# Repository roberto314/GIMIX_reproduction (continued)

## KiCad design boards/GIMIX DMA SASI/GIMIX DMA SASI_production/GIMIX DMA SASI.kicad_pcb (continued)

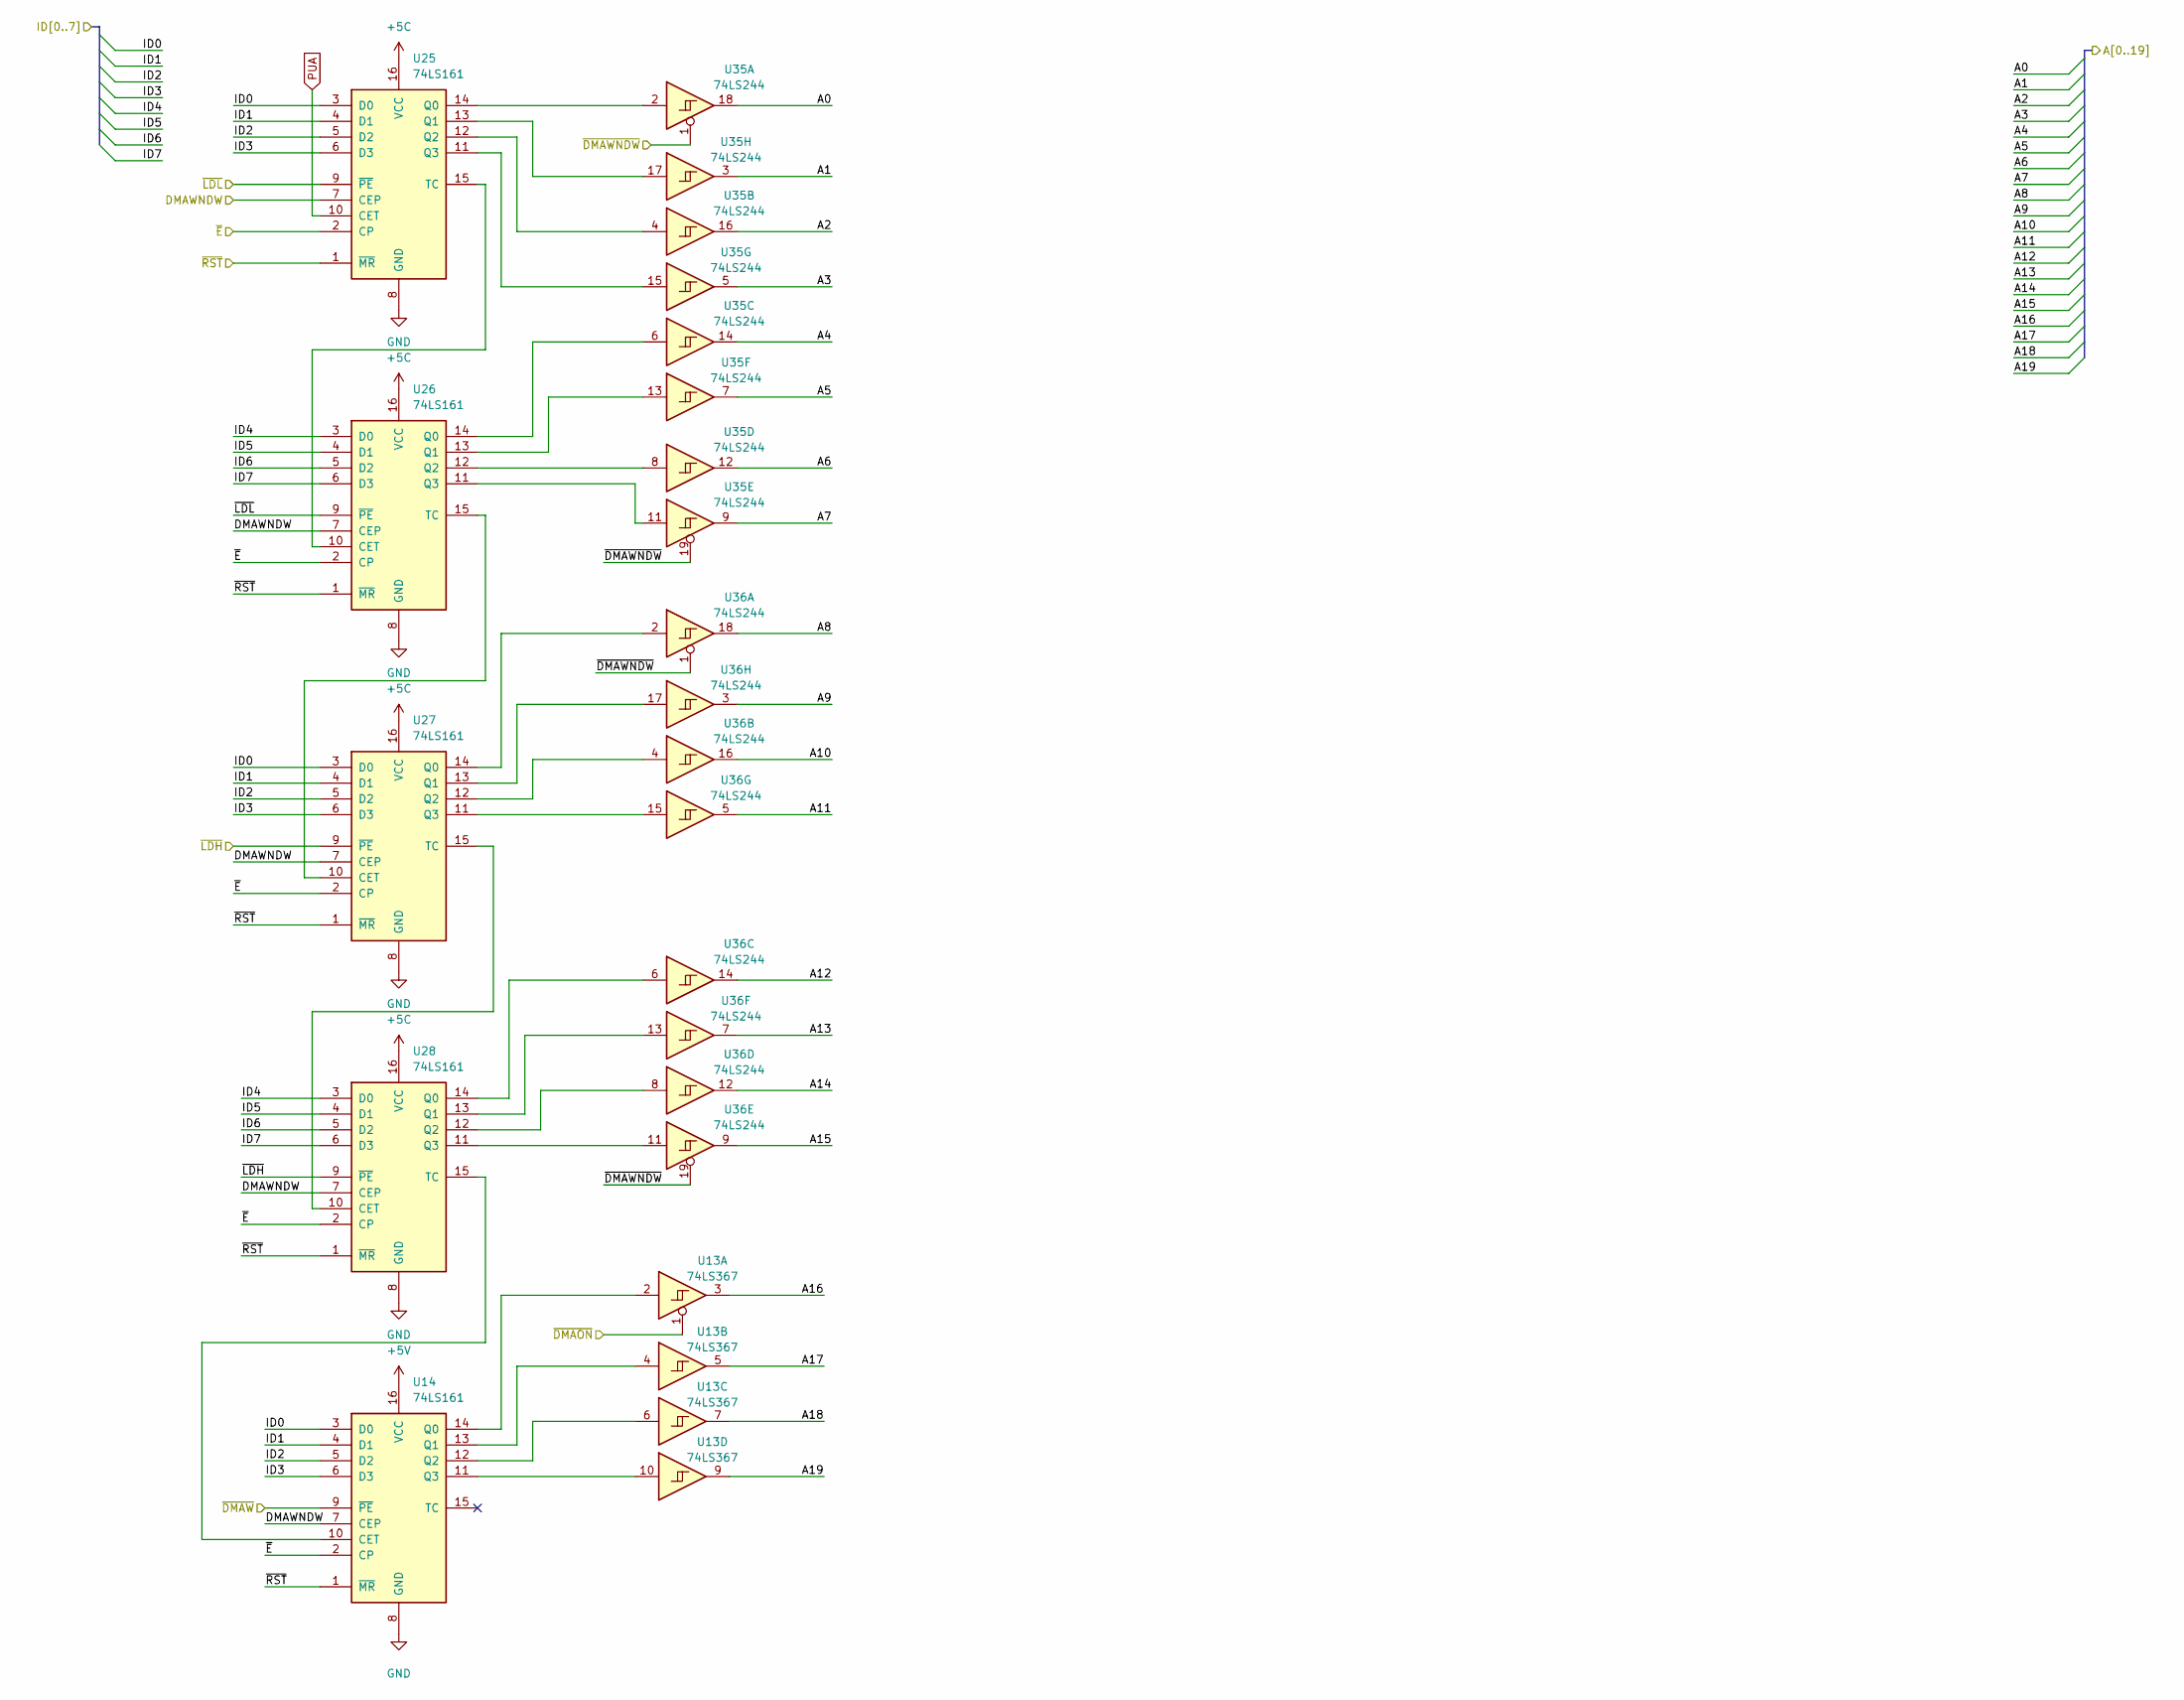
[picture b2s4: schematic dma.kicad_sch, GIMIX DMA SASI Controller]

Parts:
U13: 74LS367; DIP-16_W7.62mm
U14, U25, U26, U27, U28: 74LS161; DIP-16_W7.62mm
U35, U36: 74LS244; DIP-20_W7.62mm

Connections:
+5C: U25.16 (VCC), U26.16 (VCC), U27.16 (VCC), U28.16 (VCC); also elsewhere on the board
+5V: U14.16 (VCC); also elsewhere on the board
/A0: U35.18; also elsewhere on the board
/A1: U35.3; also elsewhere on the board
/A2: U35.16; also elsewhere on the board
/A3: U35.5; also elsewhere on the board
/A4: U35.14; also elsewhere on the board
/A5: U35.7; also elsewhere on the board
/A6: U35.12; also elsewhere on the board
/A7: U35.9; also elsewhere on the board
/A8: U36.18; also elsewhere on the board
/A9: U36.3; also elsewhere on the board
/A10: U36.16; also elsewhere on the board
/A11: U36.5; also elsewhere on the board
/A12: U36.14; also elsewhere on the board
/A13: U36.7; also elsewhere on the board
/A14: U36.12; also elsewhere on the board
/A15: U36.9; also elsewhere on the board
/A16: U13.3; also elsewhere on the board
/A17: U13.5; also elsewhere on the board
/A18: U13.7; also elsewhere on the board
/A19: U13.9; also elsewhere on the board
/DIP Switches/~DMAON: U13.1; also elsewhere on the board
/DMAWNDW: U14.7 (CEP), U25.7 (CEP), U26.7 (CEP), U27.7 (CEP), U28.7 (CEP); also elsewhere on the board
/ID0: U14.3 (D0), U25.3 (D0), U27.3 (D0); also elsewhere on the board
/ID1: U14.4 (D1), U25.4 (D1), U27.4 (D1); also elsewhere on the board
/ID2: U14.5 (D2), U25.5 (D2), U27.5 (D2); also elsewhere on the board
/ID3: U14.6 (D3), U25.6 (D3), U27.6 (D3); also elsewhere on the board
/ID4: U26.3 (D0), U28.3 (D0); also elsewhere on the board
/ID5: U26.4 (D1), U28.4 (D1); also elsewhere on the board
/ID6: U26.5 (D2), U28.5 (D2); also elsewhere on the board
/ID7: U26.6 (D3), U28.6 (D3); also elsewhere on the board
/~DMAWNDW: U35.1, U35.19, U36.1, U36.19; also elsewhere on the board
/~DMAW: U14.9 (~PE); also elsewhere on the board
/~E: U14.2 (CP), U25.2 (CP), U26.2 (CP), U27.2 (CP), U28.2 (CP); also elsewhere on the board
/~LDH: U27.9 (~PE), U28.9 (~PE); also elsewhere on the board
/~LDL: U25.9 (~PE), U26.9 (~PE); also elsewhere on the board
/~RST: U14.1 (~MR), U25.1 (~MR), U26.1 (~MR), U27.1 (~MR), U28.1 (~MR); also elsewhere on the board
GND: U14.8 (GND), U25.8 (GND), U26.8 (GND), U27.8 (GND), U28.8 (GND); also elsewhere on the board
unnamed: U14.10 (CET), U28.15 (TC)
unnamed: U13.2, U14.14 (Q0)
unnamed: U13.4, U14.13 (Q1)
unnamed: U13.6, U14.12 (Q2)
unnamed: U13.10, U14.11 (Q3)
unnamed: U25.14 (Q0), U35.2
unnamed: U25.13 (Q1), U35.17
unnamed: U25.12 (Q2), U35.4
unnamed: U25.11 (Q3), U35.15
unnamed: U25.15 (TC), U26.10 (CET)
unnamed: U26.14 (Q0), U35.6
unnamed: U26.13 (Q1), U35.13
unnamed: U26.12 (Q2), U35.8
unnamed: U26.11 (Q3), U35.11
unnamed: U26.15 (TC), U27.10 (CET)
unnamed: U27.14 (Q0), U36.2
unnamed: U27.13 (Q1), U36.17
unnamed: U27.12 (Q2), U36.4
unnamed: U27.11 (Q3), U36.15
unnamed: U27.15 (TC), U28.10 (CET)
unnamed: U28.14 (Q0), U36.6
unnamed: U28.13 (Q1), U36.13
unnamed: U28.12 (Q2), U36.8
unnamed: U28.11 (Q3), U36.11
PUA: U25.10 (CET); also elsewhere on the board

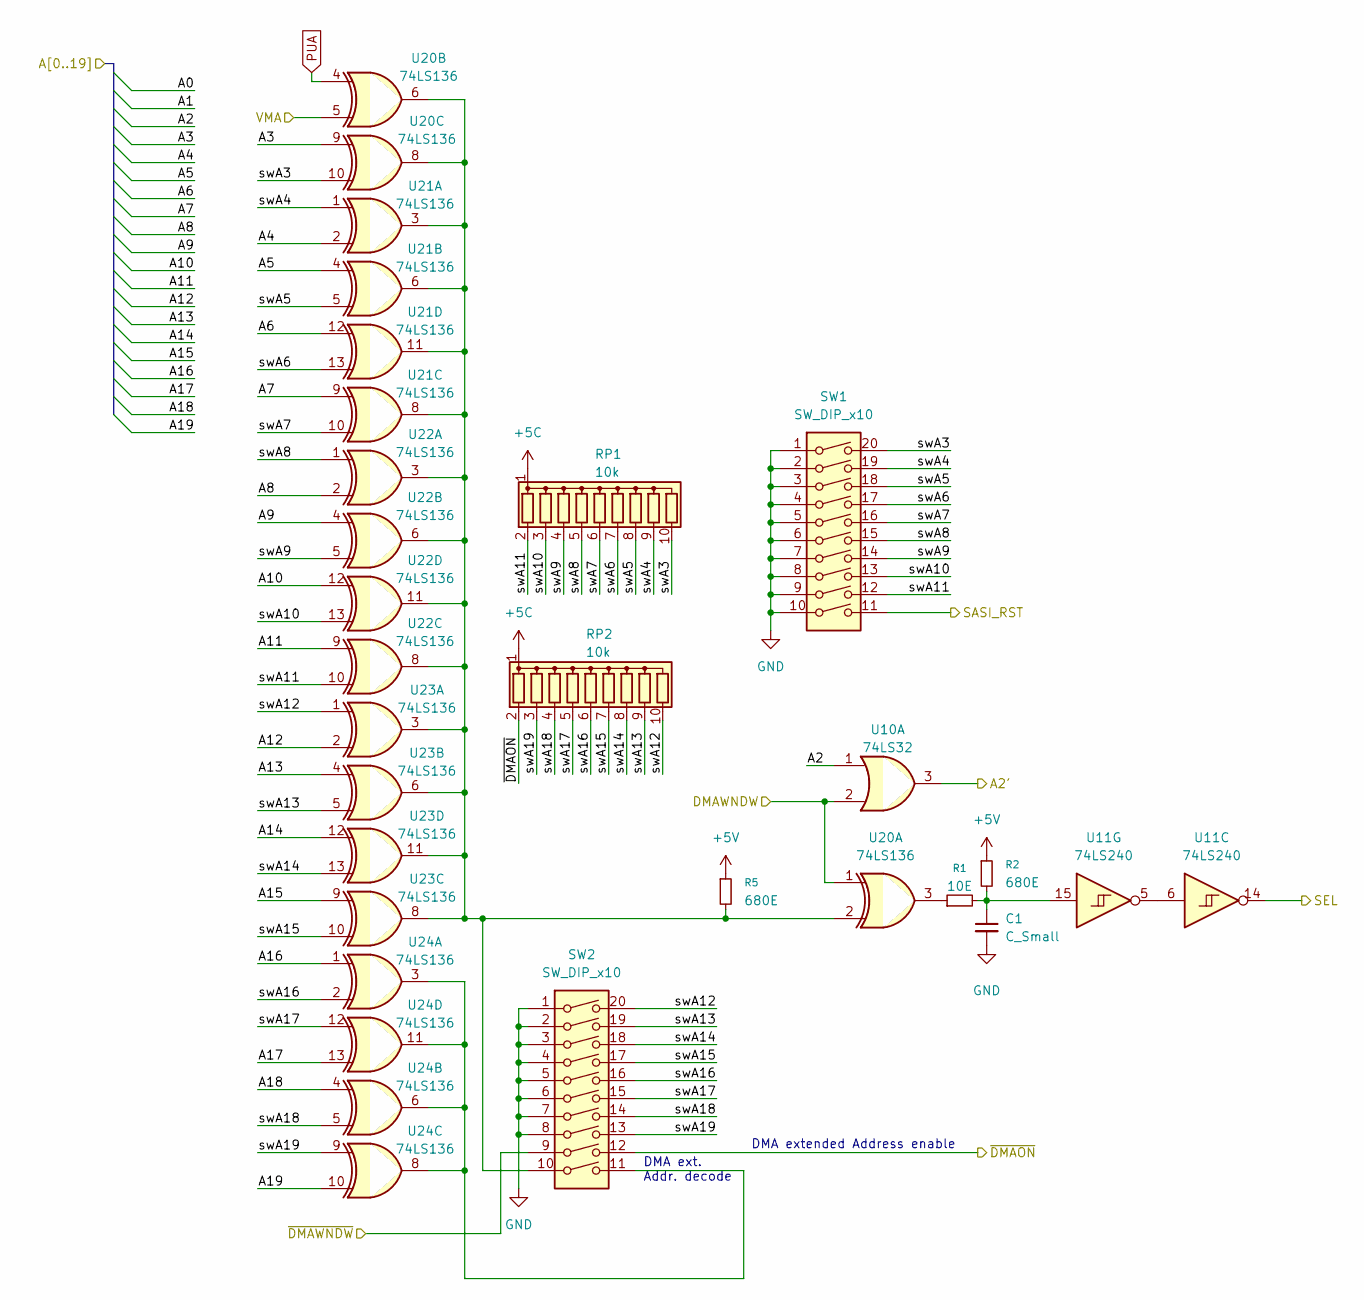
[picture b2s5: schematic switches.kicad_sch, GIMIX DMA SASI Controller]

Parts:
C1: C_Small; C_Disc_D3.0mm_W1.6mm_P2.50mm
R1: 10E; R_Axial_DIN0411_L9.9mm_D3.6mm_P12.70mm_Horizontal
R2, R5: 680E; R_Axial_DIN0411_L9.9mm_D3.6mm_P12.70mm_Horizontal
RP1, RP2: 10k; R_Array_SIP10
SW1, SW2: SW_DIP_x10; DIP-20_W7.62mm
U10: 74LS32; DIP-14_W7.62mm
U11: 74LS240; DIP-20_W7.62mm
U20, U21, U22, U23, U24: 74LS136; DIP-14_W7.62mm

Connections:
+5C: RP1.1 (common), RP2.1 (common); also elsewhere on the board
+5V: R2.1, R5.1; also elsewhere on the board
/A2: U10.1; also elsewhere on the board
/A2': U10.3; also elsewhere on the board
/A3: U20.9; also elsewhere on the board
/A4: U21.2; also elsewhere on the board
/A5: U21.4; also elsewhere on the board
/A6: U21.12; also elsewhere on the board
/A7: U21.9; also elsewhere on the board
/A8: U22.2; also elsewhere on the board
/A9: U22.4; also elsewhere on the board
/A10: U22.12; also elsewhere on the board
/A11: U22.9; also elsewhere on the board
/A12: U23.2; also elsewhere on the board
/A13: U23.4; also elsewhere on the board
/A14: U23.12; also elsewhere on the board
/A15: U23.9; also elsewhere on the board
/A16: U24.1; also elsewhere on the board
/A17: U24.13; also elsewhere on the board
/A18: U24.4; also elsewhere on the board
/A19: U24.10; also elsewhere on the board
/DIP Switches/swA3: RP1.10 (R9), SW1.20, U20.10
/DIP Switches/swA4: RP1.9 (R8), SW1.19, U21.1
/DIP Switches/swA5: RP1.8 (R7), SW1.18, U21.5
/DIP Switches/swA6: RP1.7 (R6), SW1.17, U21.13
/DIP Switches/swA7: RP1.6 (R5), SW1.16, U21.10
/DIP Switches/swA8: RP1.5 (R4), SW1.15, U22.1
/DIP Switches/swA9: RP1.4 (R3), SW1.14, U22.5
/DIP Switches/swA10: RP1.3 (R2), SW1.13, U22.13
/DIP Switches/swA11: RP1.2 (R1), SW1.12, U22.10
/DIP Switches/swA12: RP2.10 (R9), SW2.20, U23.1
/DIP Switches/swA13: RP2.9 (R8), SW2.19, U23.5
/DIP Switches/swA14: RP2.8 (R7), SW2.18, U23.13
/DIP Switches/swA15: RP2.7 (R6), SW2.17, U23.10
/DIP Switches/swA16: RP2.6 (R5), SW2.16, U24.2
/DIP Switches/swA17: RP2.5 (R4), SW2.15, U24.12
/DIP Switches/swA18: RP2.4 (R3), SW2.14, U24.5
/DIP Switches/swA19: RP2.3 (R2), SW2.13, U24.9
/DIP Switches/~DMAON: RP2.2 (R1), SW2.12; also elsewhere on the board
/DMAWNDW: U10.2, U20.1; also elsewhere on the board
/SASI_RST: SW1.11; also elsewhere on the board
/SEL: U11.14; also elsewhere on the board
/VMA: U20.5; also elsewhere on the board
/~DMAWNDW: SW2.9; also elsewhere on the board
GND: C1.2, SW1.1, SW1.2, SW1.3, SW1.4, SW1.5, SW1.6, SW1.7, SW1.8, SW1.9, SW1.10, SW2.1, SW2.2, SW2.3, SW2.4, SW2.5, SW2.6, SW2.7, SW2.8; also elsewhere on the board
unnamed: C1.1, R1.2, R2.2, U11.15
unnamed: R1.1, U20.3
unnamed: R5.2, SW2.10, U20.2, U20.6, U20.8, U21.3, U21.6, U21.8, U21.11, U22.3, U22.6, U22.8, U22.11, U23.3, U23.6, U23.8, U23.11
unnamed: SW2.11, U24.3, U24.6, U24.8, U24.11
unnamed: U11.5, U11.6
PUA: U20.4; also elsewhere on the board

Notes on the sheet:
DMA extended Address enable
DMA ext. Addr. decode

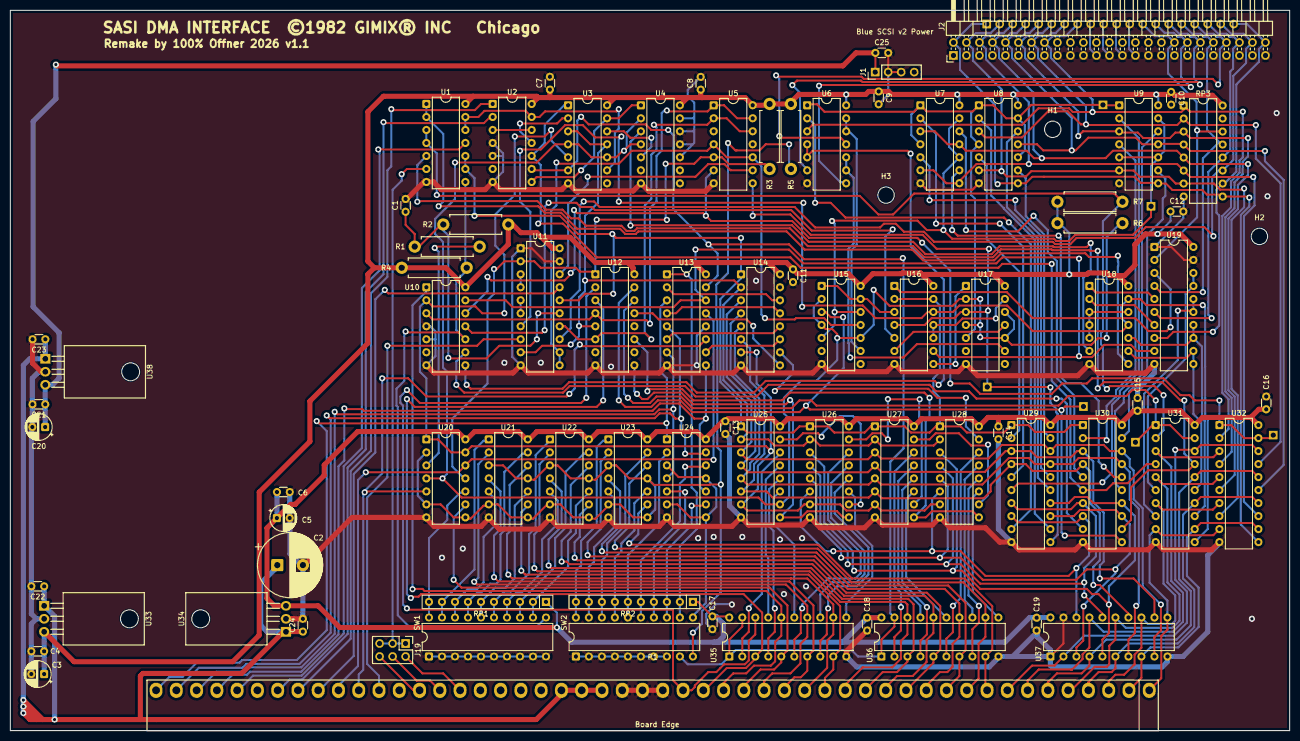
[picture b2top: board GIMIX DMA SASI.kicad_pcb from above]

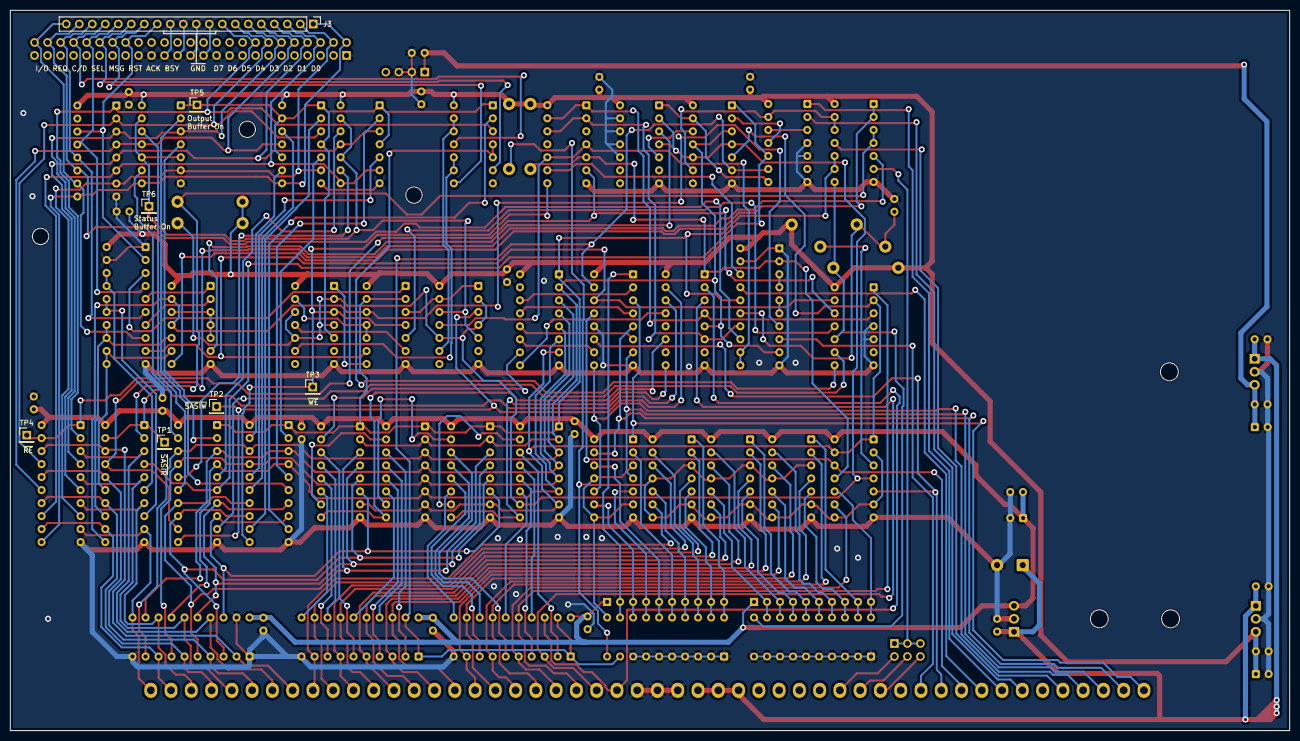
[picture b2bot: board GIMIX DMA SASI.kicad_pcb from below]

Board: 2 copper layers, 249.9 x 140.7 mm, 89 parts (7 on the bottom side), 178 nets.

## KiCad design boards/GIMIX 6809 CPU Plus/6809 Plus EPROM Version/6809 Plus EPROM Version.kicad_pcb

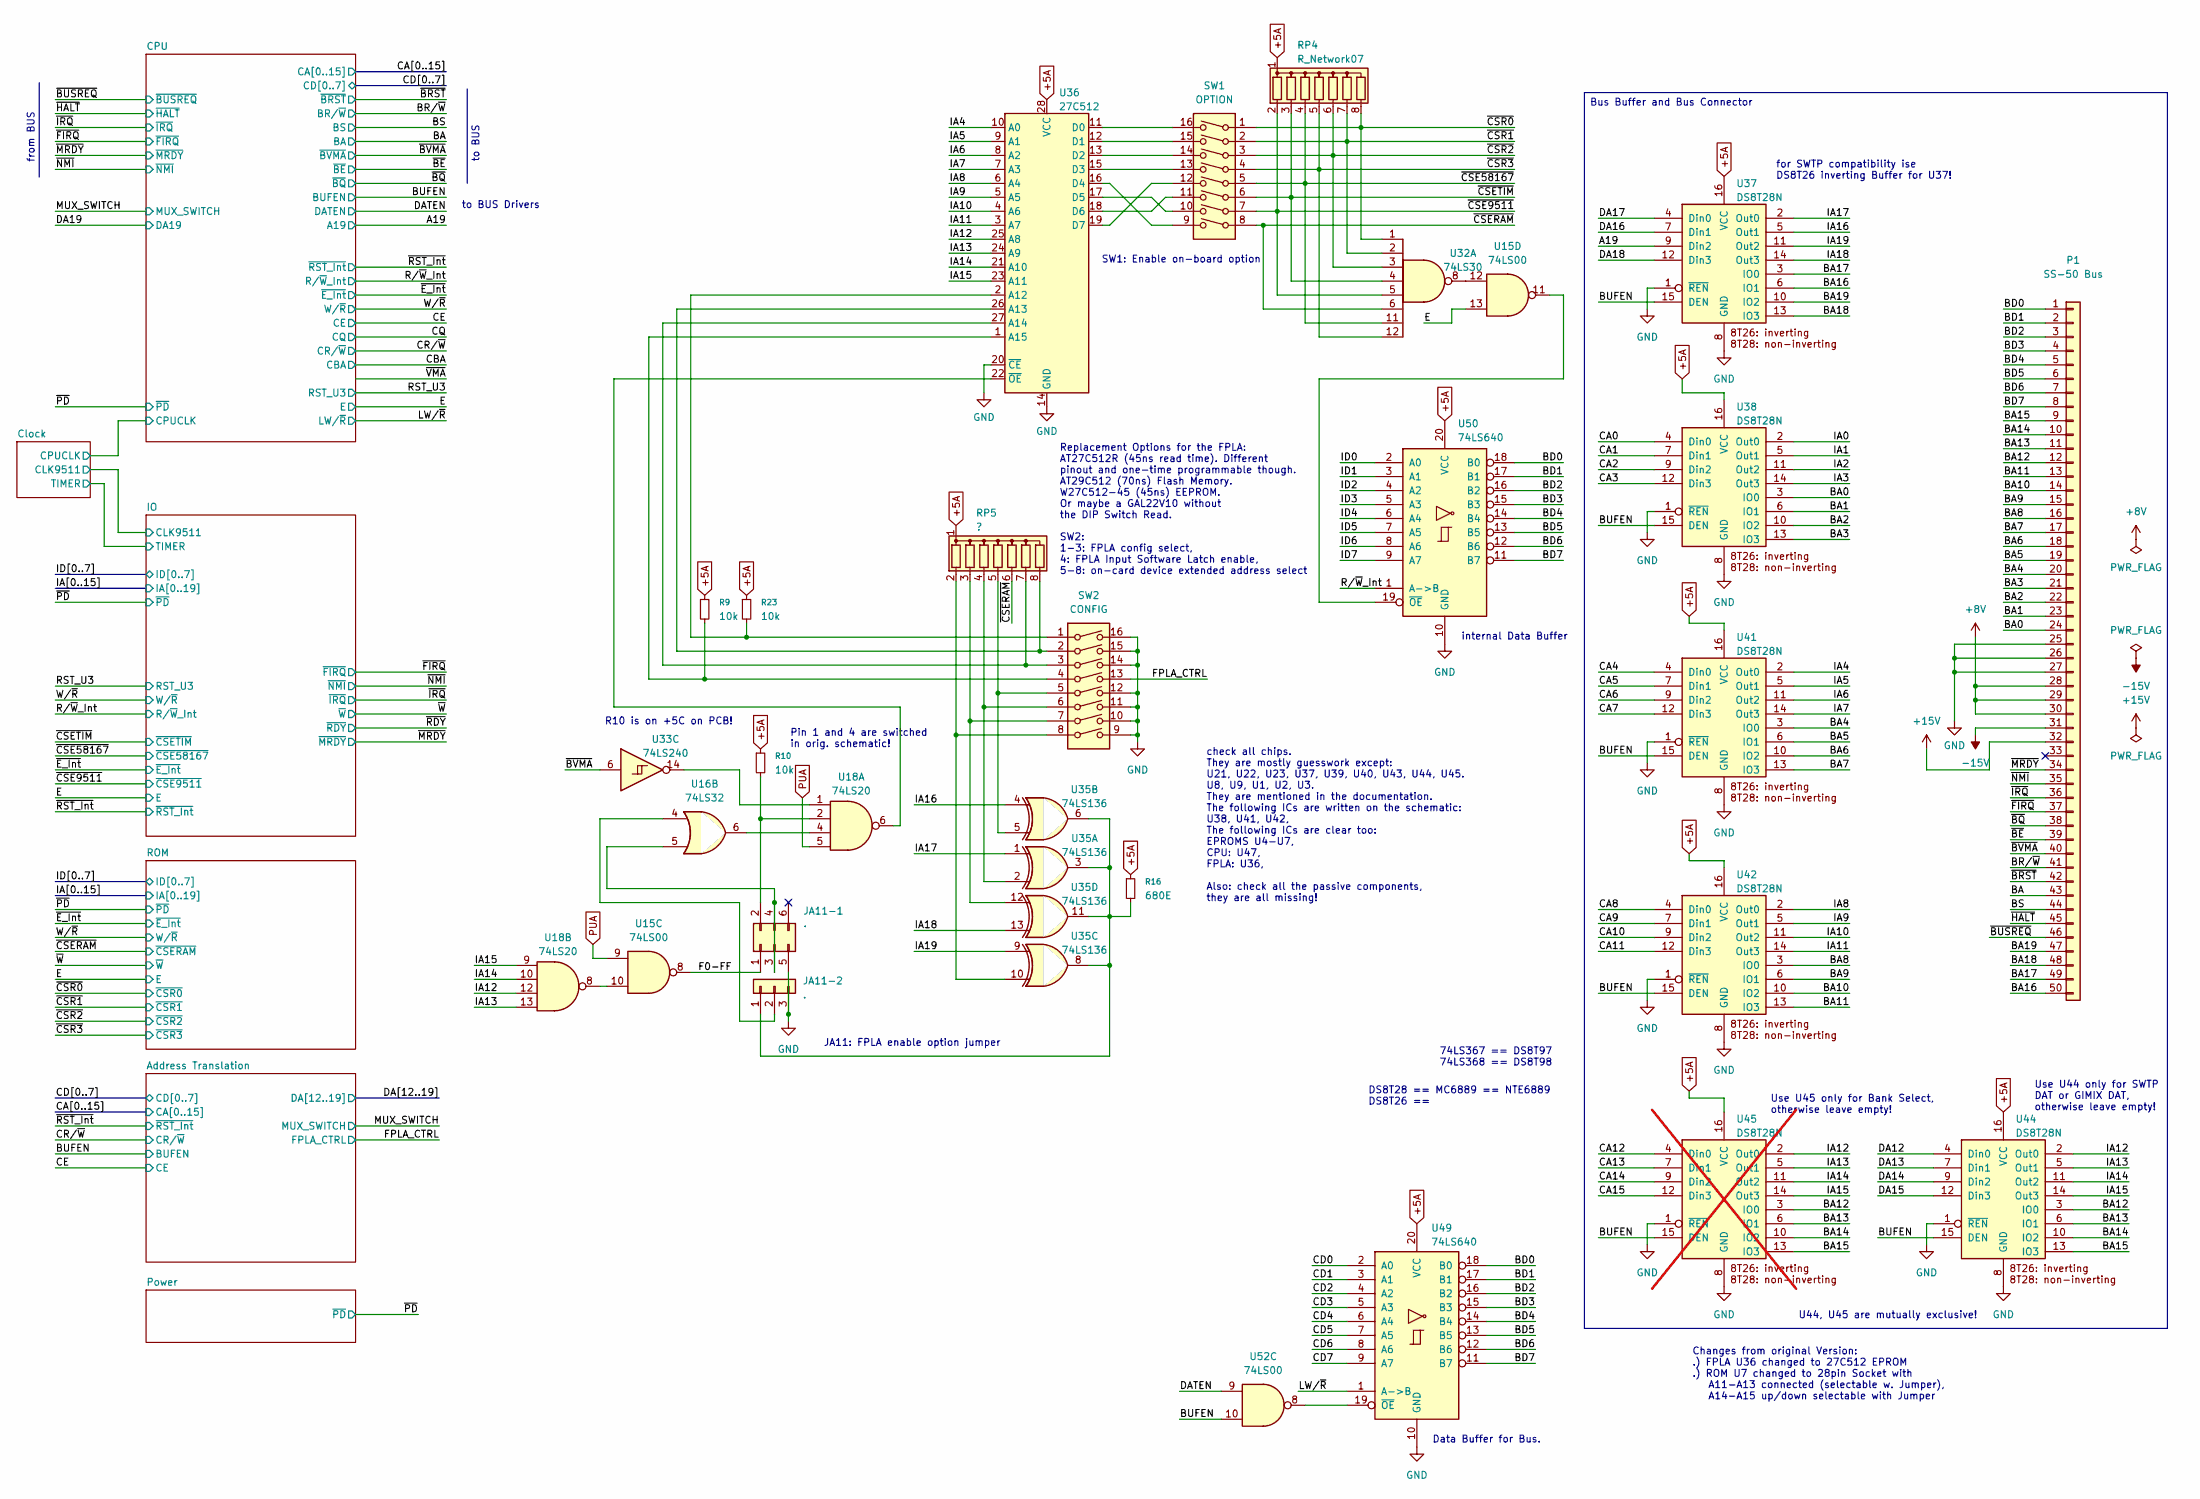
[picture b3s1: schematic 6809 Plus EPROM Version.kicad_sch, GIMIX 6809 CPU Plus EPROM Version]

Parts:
JA11-1: .; PinHeader_2x03_P2.54mm_Vertical
JA11-2: .; PinHeader_1x03_P2.54mm_Vertical
P1: SS-50 Bus; SS-50_new
R9, R10, R23: 10k; R_Axial_DIN0207_L6.3mm_D2.5mm_P10.16mm_Horizontal
R16: 680E; R_Axial_DIN0207_L6.3mm_D2.5mm_P10.16mm_Horizontal
RP4: R_Network07; R_Array_SIP8
RP5: ?; R_Array_SIP8
SW1: OPTION; DIP-16_W7.62mm
SW2: CONFIG; DIP-16_W7.62mm
U15, U52: 74LS00; DIP-14_W7.62mm
U16: 74LS32; DIP-14_W7.62mm
U18: 74LS20; DIP-14_W7.62mm
U32: 74LS30; DIP-14_W7.62mm
U33: 74LS240; DIP-20_W7.62mm
U35: 74LS136; DIP-14_W7.62mm
U36: 27C512; DIP-28_W15.24mm
U37, U38, U41, U42, U44: DS8T28N; DIP-16_W7.62mm
U45: DS8T28N; DIP-16_W7.62mm; not fitted
U49, U50: 74LS640; DIP-20_W7.62mm

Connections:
+5A: R9.1, R10.1, R16.1, R23.1, RP4.1 (common), RP5.1 (common), U36.28 (VCC), U37.16 (VCC), U38.16 (VCC), U41.16 (VCC), U42.16 (VCC), U44.16 (VCC), U45.16 (VCC), U49.20 (VCC), U50.20 (VCC); also elsewhere on the board
+8V: P1.28, P1.29, P1.30; also elsewhere on the board
+15V: P1.32; also elsewhere on the board
-15V: P1.31; also elsewhere on the board
/A19: U37.9 (Din2); also elsewhere on the board
/BA: P1.43; also elsewhere on the board
/BA0: P1.24, U38.3 (IO0)
/BA1: P1.23, U38.6 (IO1)
/BA2: P1.22, U38.10 (IO2)
/BA3: P1.21, U38.13 (IO3)
/BA4: P1.20, U41.3 (IO0)
/BA5: P1.19, U41.6 (IO1)
/BA6: P1.18, U41.10 (IO2)
/BA7: P1.17, U41.13 (IO3)
/BA8: P1.16, U42.3 (IO0)
/BA9: P1.15, U42.6 (IO1)
/BA10: P1.14, U42.10 (IO2)
/BA11: P1.13, U42.13 (IO3)
/BA12: P1.12, U44.3 (IO0), U45.3 (IO0)
/BA13: P1.11, U44.6 (IO1), U45.6 (IO1)
/BA14: P1.10, U44.10 (IO2), U45.10 (IO2)
/BA15: P1.9, U44.13 (IO3), U45.13 (IO3)
/BA16: P1.50, U37.6 (IO1)
/BA17: P1.49, U37.3 (IO0)
/BA18: P1.48, U37.13 (IO3)
/BA19: P1.47, U37.10 (IO2)
/BD0: P1.1, U49.18 (B0), U50.18 (B0)
/BD1: P1.2, U49.17 (B1), U50.17 (B1)
/BD2: P1.3, U49.16 (B2), U50.16 (B2)
/BD3: P1.4, U49.15 (B3), U50.15 (B3)
/BD4: P1.5, U49.14 (B4), U50.14 (B4)
/BD5: P1.6, U49.13 (B5), U50.13 (B5)
/BD6: P1.7, U49.12 (B6), U50.12 (B6)
/BD7: P1.8, U49.11 (B7), U50.11 (B7)
/BR/~W: P1.41; also elsewhere on the board
/BS: P1.44; also elsewhere on the board
/BUFEN: U37.15 (DEN), U38.15 (DEN), U41.15 (DEN), U42.15 (DEN), U44.15 (DEN), U45.15 (DEN), U52.10; also elsewhere on the board
/CA0: U38.4 (Din0); also elsewhere on the board
/CA1: U38.7 (Din1); also elsewhere on the board
/CA2: U38.9 (Din2); also elsewhere on the board
/CA3: U38.12 (Din3); also elsewhere on the board
/CA4: U41.4 (Din0); also elsewhere on the board
/CA5: U41.7 (Din1); also elsewhere on the board
/CA6: U41.9 (Din2); also elsewhere on the board
/CA7: U41.12 (Din3); also elsewhere on the board
/CA8: U42.4 (Din0); also elsewhere on the board
/CA9: U42.7 (Din1); also elsewhere on the board
/CA10: U42.9 (Din2); also elsewhere on the board
/CA11: U42.12 (Din3); also elsewhere on the board
/CA12: U45.4 (Din0); also elsewhere on the board
/CA13: U45.7 (Din1); also elsewhere on the board
/CA14: U45.9 (Din2); also elsewhere on the board
/CA15: U45.12 (Din3); also elsewhere on the board
/CD0: U49.2 (A0); also elsewhere on the board
/CD1: U49.3 (A1); also elsewhere on the board
/CD2: U49.4 (A2); also elsewhere on the board
/CD3: U49.5 (A3); also elsewhere on the board
/CD4: U49.6 (A4); also elsewhere on the board
/CD5: U49.7 (A5); also elsewhere on the board
/CD6: U49.8 (A6); also elsewhere on the board
/CD7: U49.9 (A7); also elsewhere on the board
/DA12: U44.4 (Din0); also elsewhere on the board
/DA13: U44.7 (Din1); also elsewhere on the board
/DA14: U44.9 (Din2); also elsewhere on the board
/DA15: U44.12 (Din3); also elsewhere on the board
/DA16: U37.7 (Din1); also elsewhere on the board
/DA17: U37.4 (Din0); also elsewhere on the board
/DA18: U37.12 (Din3); also elsewhere on the board
/DATEN: U52.9; also elsewhere on the board
/E: U15.13; also elsewhere on the board
/F0-FF: JA11-1.1, U15.8
/FPLA_CTRL: SW2.13; also elsewhere on the board
/IA0: U38.2 (Out0); also elsewhere on the board
/IA1: U38.5 (Out1); also elsewhere on the board
/IA2: U38.11 (Out2); also elsewhere on the board
/IA3: U38.14 (Out3); also elsewhere on the board
/IA4: U36.10 (A0), U41.2 (Out0); also elsewhere on the board
/IA5: U36.9 (A1), U41.5 (Out1); also elsewhere on the board
/IA6: U36.8 (A2), U41.11 (Out2); also elsewhere on the board
/IA7: U36.7 (A3), U41.14 (Out3); also elsewhere on the board
/IA8: U36.6 (A4), U42.2 (Out0); also elsewhere on the board
/IA9: U36.5 (A5), U42.5 (Out1); also elsewhere on the board
/IA10: U36.4 (A6), U42.11 (Out2); also elsewhere on the board
/IA11: U36.3 (A7), U42.14 (Out3); also elsewhere on the board
/IA12: U18.12, U36.25 (A8), U44.2 (Out0), U45.2 (Out0); also elsewhere on the board
/IA13: U18.13, U36.24 (A9), U44.5 (Out1), U45.5 (Out1); also elsewhere on the board
/IA14: U18.10, U36.21 (A10), U44.11 (Out2), U45.11 (Out2)
/IA15: U18.9, U36.23 (A11), U44.14 (Out3), U45.14 (Out3)
/IA16: U35.4, U37.5 (Out1)
/IA17: U35.1, U37.2 (Out0)
/IA18: U35.13, U37.14 (Out3)
/IA19: U35.9, U37.11 (Out2)
/ID0: U50.2 (A0); also elsewhere on the board
/ID1: U50.3 (A1); also elsewhere on the board
/ID2: U50.4 (A2); also elsewhere on the board
/ID3: U50.5 (A3); also elsewhere on the board
/ID4: U50.6 (A4); also elsewhere on the board
/ID5: U50.7 (A5); also elsewhere on the board
/ID6: U50.8 (A6); also elsewhere on the board
/ID7: U50.9 (A7); also elsewhere on the board
/LW/~R: U49.1 (A->B); also elsewhere on the board
/R/~W_Int: U50.1 (A->B); also elsewhere on the board
/~BE: P1.39; also elsewhere on the board
/~BQ: P1.38; also elsewhere on the board
/~BRST: P1.42; also elsewhere on the board
/~BUSREQ: P1.46; also elsewhere on the board
/~BVMA: P1.40, U33.6; also elsewhere on the board
/~CSE9511: RP4.2 (R1), SW1.7, U32.5; also elsewhere on the board
/~CSE58167: RP4.4 (R3), SW1.5, U32.11; also elsewhere on the board
/~CSERAM: RP5.6 (R5), SW1.8, U32.6; also elsewhere on the board
/~CSETIM: RP4.3 (R2), SW1.6, U32.4; also elsewhere on the board
/~CSR0: RP4.8 (R7), SW1.1, U32.1; also elsewhere on the board
/~CSR1: RP4.7 (R6), SW1.2, U32.2; also elsewhere on the board
/~CSR2: RP4.6 (R5), SW1.3, U32.3; also elsewhere on the board
/~CSR3: RP4.5 (R4), SW1.4, U32.12; also elsewhere on the board
/~FIRQ: P1.37; also elsewhere on the board
/~HALT: P1.45; also elsewhere on the board
/~IRQ: P1.36; also elsewhere on the board
/~MRDY: P1.34; also elsewhere on the board
/~NMI: P1.35; also elsewhere on the board
GND: JA11-1.5, JA11-2.3, P1.25, P1.26, P1.27, SW2.9, SW2.10, SW2.11, SW2.12, SW2.14, SW2.15, SW2.16, U36.14 (GND), U36.20 (~CE), U37.1 (~REN), U37.8 (GND), U38.1 (~REN), U38.8 (GND), U41.1 (~REN), U41.8 (GND), U42.1 (~REN), U42.8 (GND), U44.1 (~REN), U44.8 (GND), U45.1 (~REN), U45.8 (GND), U49.10 (GND), U50.10 (GND); also elsewhere on the board
unnamed: JA11-1.2, R10.2, U18.2
unnamed: JA11-1.3, JA11-1.4, U16.5
unnamed: JA11-2.1, R16.2, U35.3, U35.6, U35.8, U35.11
unnamed: JA11-2.2, U16.4
unnamed: RP5.2 (R1), SW2.8, U35.10
unnamed: RP5.3 (R2), SW2.7, U35.12
unnamed: RP5.4 (R3), SW2.6, U35.2
unnamed: RP5.5 (R4), SW2.5, U35.5
unnamed: RP5.7 (R6), SW2.3, U36.27 (A14)
unnamed: RP5.8 (R7), SW2.2, U36.26 (A13)
unnamed: U15.10, U18.8
unnamed: U15.12, U32.8
unnamed: U16.6, U18.4
unnamed: U18.1, U33.14
unnamed: R23.2, SW2.1, U36.2 (A12)
unnamed: R9.2, SW2.4, U36.1 (A15)
unnamed: SW1.16, U36.11 (D0)
unnamed: SW1.15, U36.12 (D1)
unnamed: SW1.14, U36.13 (D2)
unnamed: SW1.13, U36.15 (D3)
unnamed: SW1.9, U36.16 (D4)
unnamed: SW1.10, U36.17 (D5)
unnamed: SW1.11, U36.18 (D6)
unnamed: SW1.12, U36.19 (D7)
unnamed: U18.6, U36.22 (~OE)
unnamed: U49.19 (~OE), U52.8
unnamed: U15.11, U50.19 (~OE)
PUA: U15.9, U18.5; also elsewhere on the board

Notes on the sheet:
from BUS
Use U45 only for Bank Select, otherwise leave empty!
to BUS Drivers
Replacement Options for the FPLA: AT27C512R (45ns read time). Different pinout and one-time programmable though. AT29C512 (70ns) Flash Memory. W27C512-45 (45ns) EEPROM. Or maybe a GAL22V10 without the DIP Switch Read.
SW1: Enable on-board option
check all chips. They are mostly guesswork except: U21, U22, U23, U37, U39, U40, U43, U44, U45. U8, U9, U1, U2, U3. They are mentioned in the documentation. The following ICs are written on the schematic: U38, U41, U42, The following ICs are clear too: EPROMS U4-U7, CPU: U47, FPLA: U36, Also: check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
Changes from original Version: .) FPLA U36 changed to 27C512 EPROM .) ROM U7 changed to 28pin Socket with A11-A13 connected (selectable w. Jumper), A14-A15 up/down selectable with Jumper
U44, U45 are mutually exclusive!
DS8T28 == MC6889 == NTE6889 DS8T26 ==
Use U44 only for SWTP DAT or GIMIX DAT, otherwise leave empty!
for SWTP compatibility ise DS8T26 inverting Buffer for U37!
R10 is on +5C on PCB!
SW2: 1-3: FPLA config select, 4: FPLA Input Software Latch enable, 5-8: on-card device extended address select
internal Data Buffer
74LS367 == DS8T97 74LS368 == DS8T98
JA11: FPLA enable option jumper
Pin 1 and 4 are switched in orig. schematic!
Data Buffer for Bus.
to BUS
Bus Buffer and Bus Connector
